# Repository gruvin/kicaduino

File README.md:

# KiCADuino
### A KiCAD version of the infamous Arduino UNO r3 PCB

There are too few, readily available and open projects in <a href='http://www.kicad-pcb.org'>KiCAD</a> 
format. I'm working to change that -- by taking some I like and re-creating them in KiCAD.

Why? Well, because it seemed a good idea and I seemed to have the time.

I'm starting with the good old Arduino UNO Rev.3, reference design. Obviously, my KiCAD version will not be an 
exact copy. In fact, I'll probably change the USB connector to USB-B-mini SMD. But otherwise, the circuitry 
will be the same, down to the socketed, DIP 'mega328. Maybe I'll do other versions later.

<blockquote>Arduino(TM) is a trademark of the owners of www.arduino.cc (they don't seem to have a name, other 
than Arduino -- even on their trademark information page). This KiCAD re-creation is by a 
separate individual, who is in no way related to the Arduino trademark owners or even likely 
known to them. Please see www.arduino.cc for all official Arduino(TM) information.</blockquote>

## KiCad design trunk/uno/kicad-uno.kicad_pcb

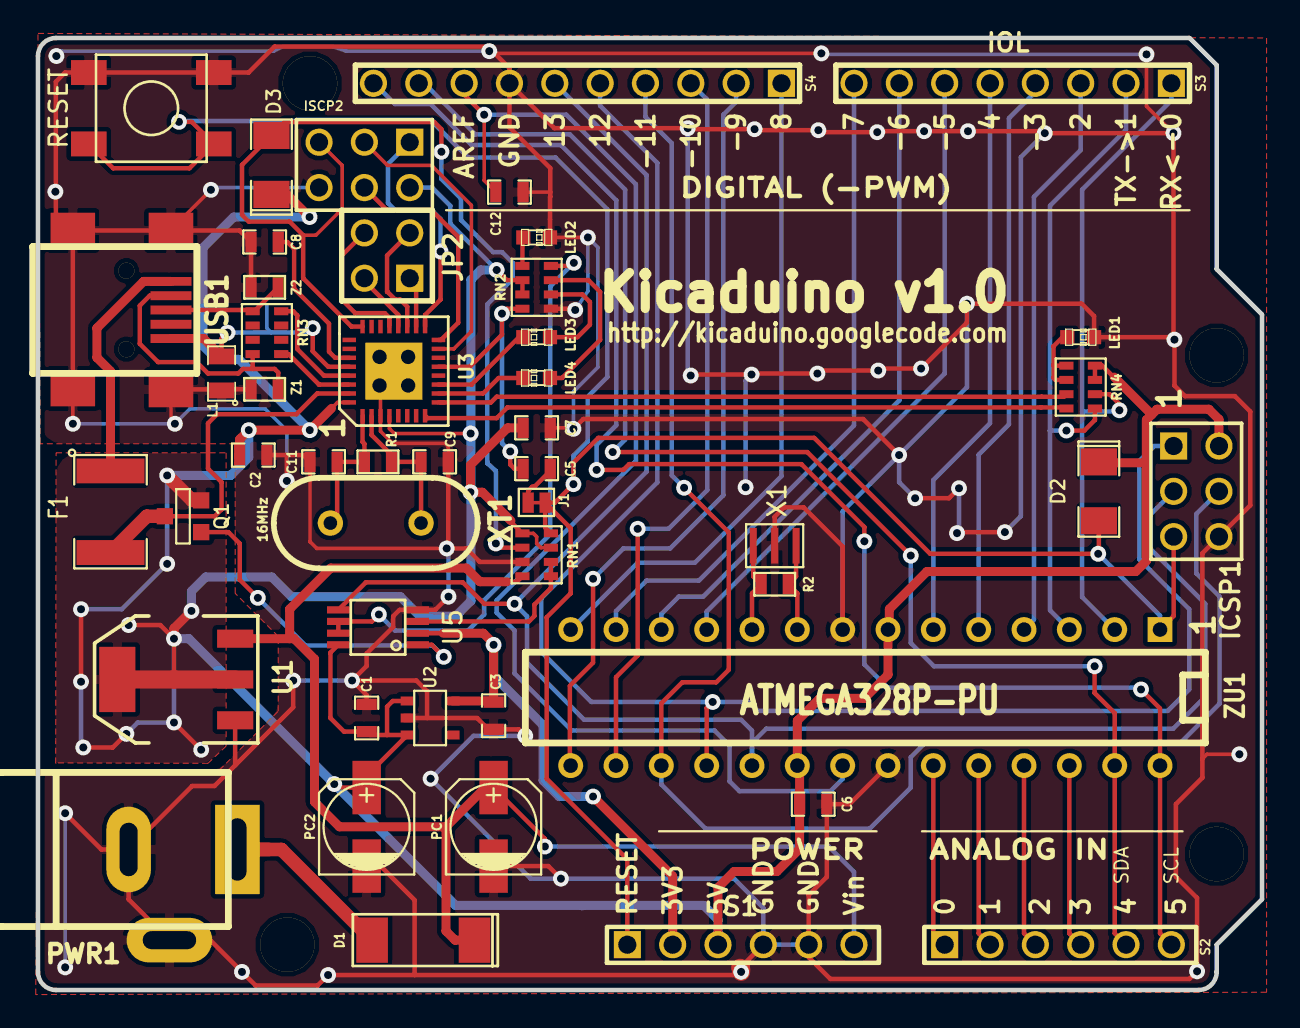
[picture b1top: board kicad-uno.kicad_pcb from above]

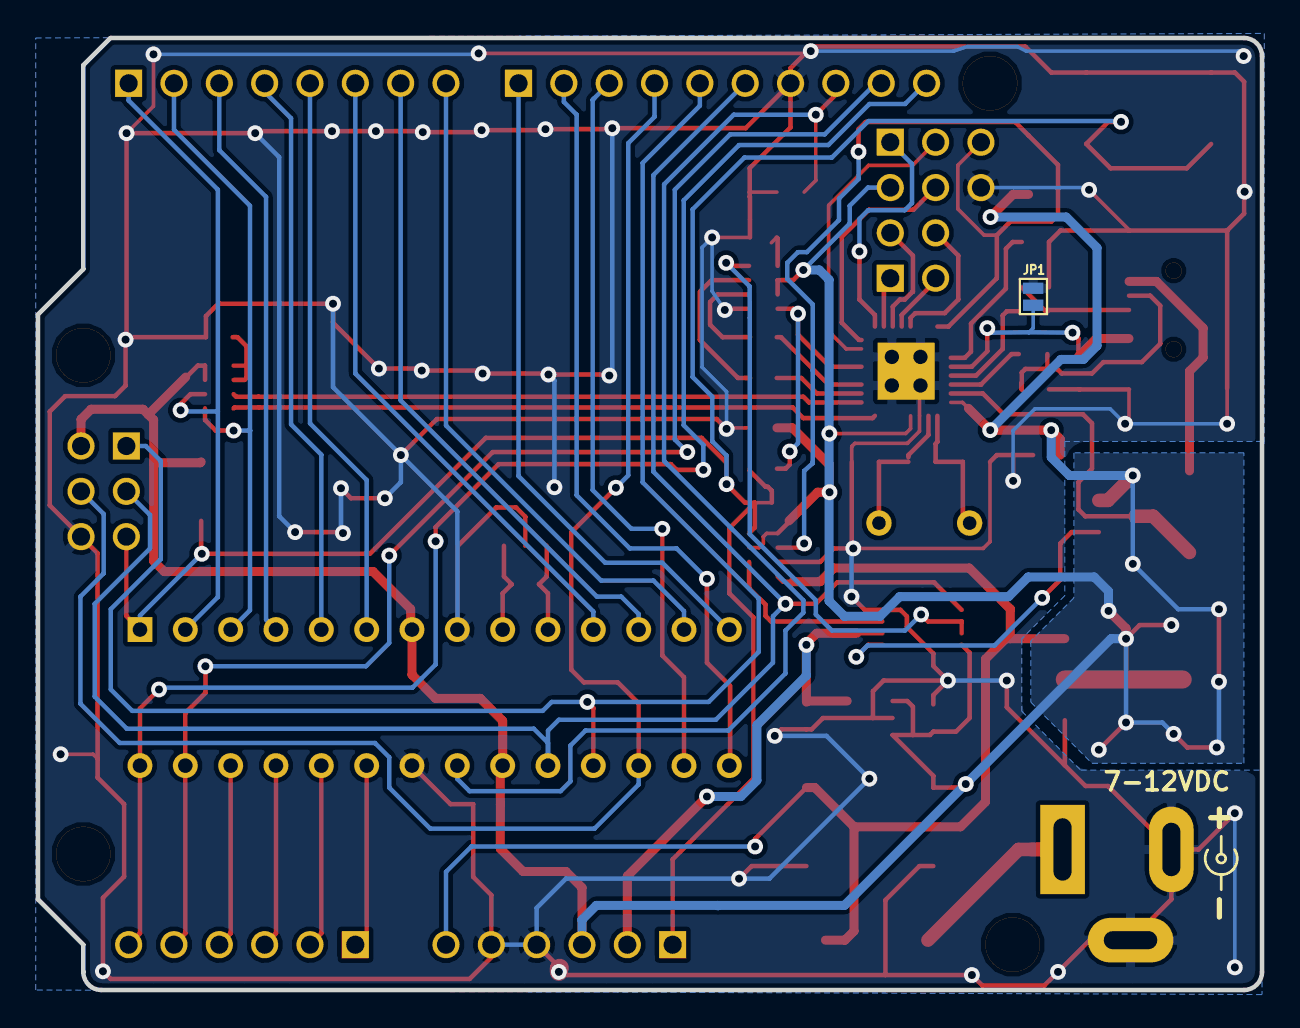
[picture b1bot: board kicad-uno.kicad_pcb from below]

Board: 2 copper layers, 68.6 x 53.3 mm, 54 parts (2 on the bottom side), 59 nets.

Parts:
C1, C2, C5, C6, C7, C12: 100n; SM0603_Capa
C3, C8: 1u; SM0603_Capa
C9, C11: 22p; SM0603_Capa
D1: M7; DO-214AC
D2, D3: CD1206-S01575; SM1206D
F1: MF-MSMF050-2 500mA; SM1812
HOLE_130x130mil, HOLE_130x130mil#2, HOLE_130x130mil#3, HOLE_130x250mil: VAL**; HOLE_120x120mil
ICSP1: 3X2 M; pin_array_3x2
ISCP2: 3X2 M; pin_array_3x2
J1: RESET_EN; JSOLD
JP1: Solder Bridge; JSOLD
JP2: 2X2 M; PIN_ARRAY_2X2
L1: FERRITE; SM0805
LED1: GREEN; LED_0603_GREEN
LED2, LED3, LED4: YELLOW; LED_0603_YEL
PC1, PC2: 47u 25V; c_elec_5x5.8
PWR1: POWER_JACK; JACK_NEB21R
Q1: FDN340P; SOT23GDS
R1, R2: 1M; SM0603
REF: VAL**; POWER_POLARITY_REF
RN1: 10K; RN_0603x4
RN2, RN4: 1K; RN_0603x4
RN3: 22R; RN_0603x4
S1: PWR; pin_array_6x1
S2: AD; pin_array_6x1
S3: IOL; pin_array_8x1
S4: IOH; pin_array_10x1
SW1: RESET; SWPUSH_SPST_SMD
U1: NCP1117 5V; SOT223
U2: LP2985-33DBVR; SOT23-5
U3: ATMEGA16U2-MU(R); QFN32_2x2-SINK
U5: LM358; SSOP8
USB1: USB-MINI-AB; USB-B_mini
X1: CSTCE16M0V53 16MHz; CSTCE_V13C
XT1: 16MHz; HC-49V
Z1, Z2: CG0603MLC-05E 5V; SM0603
ZU1: ATMEGA328P-PU; DIP-28__300

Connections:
+3V3: C3.1, S1.2, U2.5, U5.2
+5V: C1.1, C2.1, C6.1, C7.1, D2.2, D3.2, ICSP1.2, ISCP2.2, PC2.1, Q1.S, RN1.3, RN1.5, RN2.2, RN2.3, RN4.3, RN4.4, S1.3, U1.2, U1.4, U2.1, U2.3, U3.4, U3.32, U5.8, ZU1.7, ZU1.20
/AD0: S2.1, ZU1.23
/AD1: S2.2, ZU1.24
/AD2: S2.3, ZU1.25
/AD3: S2.4, ZU1.26
/AD4/SDA: S2.5, S4.9, ZU1.27
/AD5/SCL: S2.6, S4.10, ZU1.28
/IO0: RN4.2, S3.1, ZU1.2
/IO1: RN4.1, S3.2, ZU1.3
/IO2: S3.3, ZU1.4
/IO3: S3.4, ZU1.5
/IO4: S3.5, ZU1.6
/IO5: S3.6, ZU1.11
/IO6: S3.7, ZU1.12
/IO7: S3.8, ZU1.13
/IO8: S4.1, ZU1.14
/IO9: S4.2, ZU1.15
/POWER/CMP: RN1.1, RN1.2, U5.3
/RESET: C5.2, D2.1, ICSP1.5, J1.1, J1.2, RN1.4, S1.1, SW1.3, SW1.4, ZU1.1
/SS: S4.3, ZU1.16
/USB/D+: RN3.5, USB1.3, Z2.1
/USB/D-: RN3.8, USB1.2, Z1.1
/USB/MISO2: ISCP2.1, U3.17
/USB/MOSI2: ISCP2.4, U3.16
/USB/RESET2: D3.1, ISCP2.5, RN1.6, U3.24
/USB/RXLED: LED4.2, U3.10
/USB/SCK2: ISCP2.3, U3.15
/USB/TXLED: LED3.2, U3.11
AREF: C12.1, S4.8, ZU1.21
DTR: C5.1, RN2.4, U3.13
GND: C1.2, C2.2, C3.2, C6.2, C7.2, C8.2, C9.2, C11.2, C12.2, ICSP1.6, ISCP2.6, JP1.1, L1.1, LED1.2, LED2.2, PC1.2, PC2.2, PWR1.2, PWR1.3, RN1.7, RN2.5, S1.4, S1.5, S4.7, SW1.1, SW1.2, U1.1, U2.2, U3.3, U3.33, U5.4, USB1.6, USB1.7, USB1.8, USB1.9, X1.2, Z1.2, Z2.2, ZU1.8, ZU1.22
unnamed: ICSP1.4, S4.4, ZU1.17
unnamed: ICSP1.1, S4.5, ZU1.18
unnamed: R2.1, X1.1, ZU1.10
unnamed: R2.2, X1.3, ZU1.9
unnamed: Q1.G, U5.1
unnamed: LED2.1, RN2.1
unnamed: RN2.8, U5.6, U5.7
unnamed: LED1.1, RN4.5, RN4.6
unnamed: D1.1, PWR1.1
unnamed: JP2.4, U3.21
unnamed: JP2.3, U3.19
unnamed: JP2.2, U3.20
unnamed: C8.1, U3.27
unnamed: JP2.1, U3.18
unnamed: LED3.1, RN2.6
unnamed: F1.1, USB1.1
unnamed: LED4.1, RN2.7
unnamed: RN3.4, U3.29
unnamed: RN3.1, U3.30
unnamed: C9.1, R1.1, U3.2, XT1.2
unnamed: C11.1, R1.2, U3.1, XT1.1
unnamed: JP1.2, L1.2, U3.28, USB1.5
RXD: RN4.7, U3.9
SCK: ICSP1.3, S4.6, U5.5, ZU1.19
TXD: RN4.8, U3.8
USBVCC: F1.2, Q1.D, U3.31
VIN: D1.2, PC1.1, RN1.8, S1.6, U1.3

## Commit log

2013-07-24 Initial directory structure.
2013-07-24 Schematic ERC passes. Circuit _might_ be complete, without errors. You just never know. :-P
2013-07-25 Component packages configured.
    PCB initial placement.
    Some minor typo corrections.
2013-07-25 Added resistor network part/module for RN1-4 (no 3D package yet).
2013-07-25 Board edges completed.
2013-07-25 About half the comoponents placed, in the exact same location as the UNO Rev3 reference design, except I changed the USB socket to a mini.
    A number of minor schematic errors were corrected, around the pin
    numbering of the four resistor network chips.
2013-07-26 All components placed. Some routing started.
2013-07-27 More routing.
2013-07-27 Routing complete. Board complete.
    Just need to do the 3D packages for the resistor arrays and rsonator.
    Oh -- the previous revisions had the wrong size resistor array parts. That
    was corrected in this version. (SM0402, apparently.)
2013-07-28 Board fully completed v1.0.
2013-07-28 wiki image
2013-07-28 Mounting holes added. Had to move the power jack out a bit.
2013-07-29 Changed the resistor networks from 0402 to 0603 size, per the original Arduino UNO reference design (I think!)
2013-07-29 Previous change may not have been fully saved. Fixed in this commit.
2013-07-29 Minor track spacing changes, just to reduce copper etch some.
2015-06-03 Added image
2016-11-25 UNO production files
